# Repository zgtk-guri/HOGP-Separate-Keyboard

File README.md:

# HOGP-Separate-Keyboard
A separate keyboard with nRF51 and DAP-Link

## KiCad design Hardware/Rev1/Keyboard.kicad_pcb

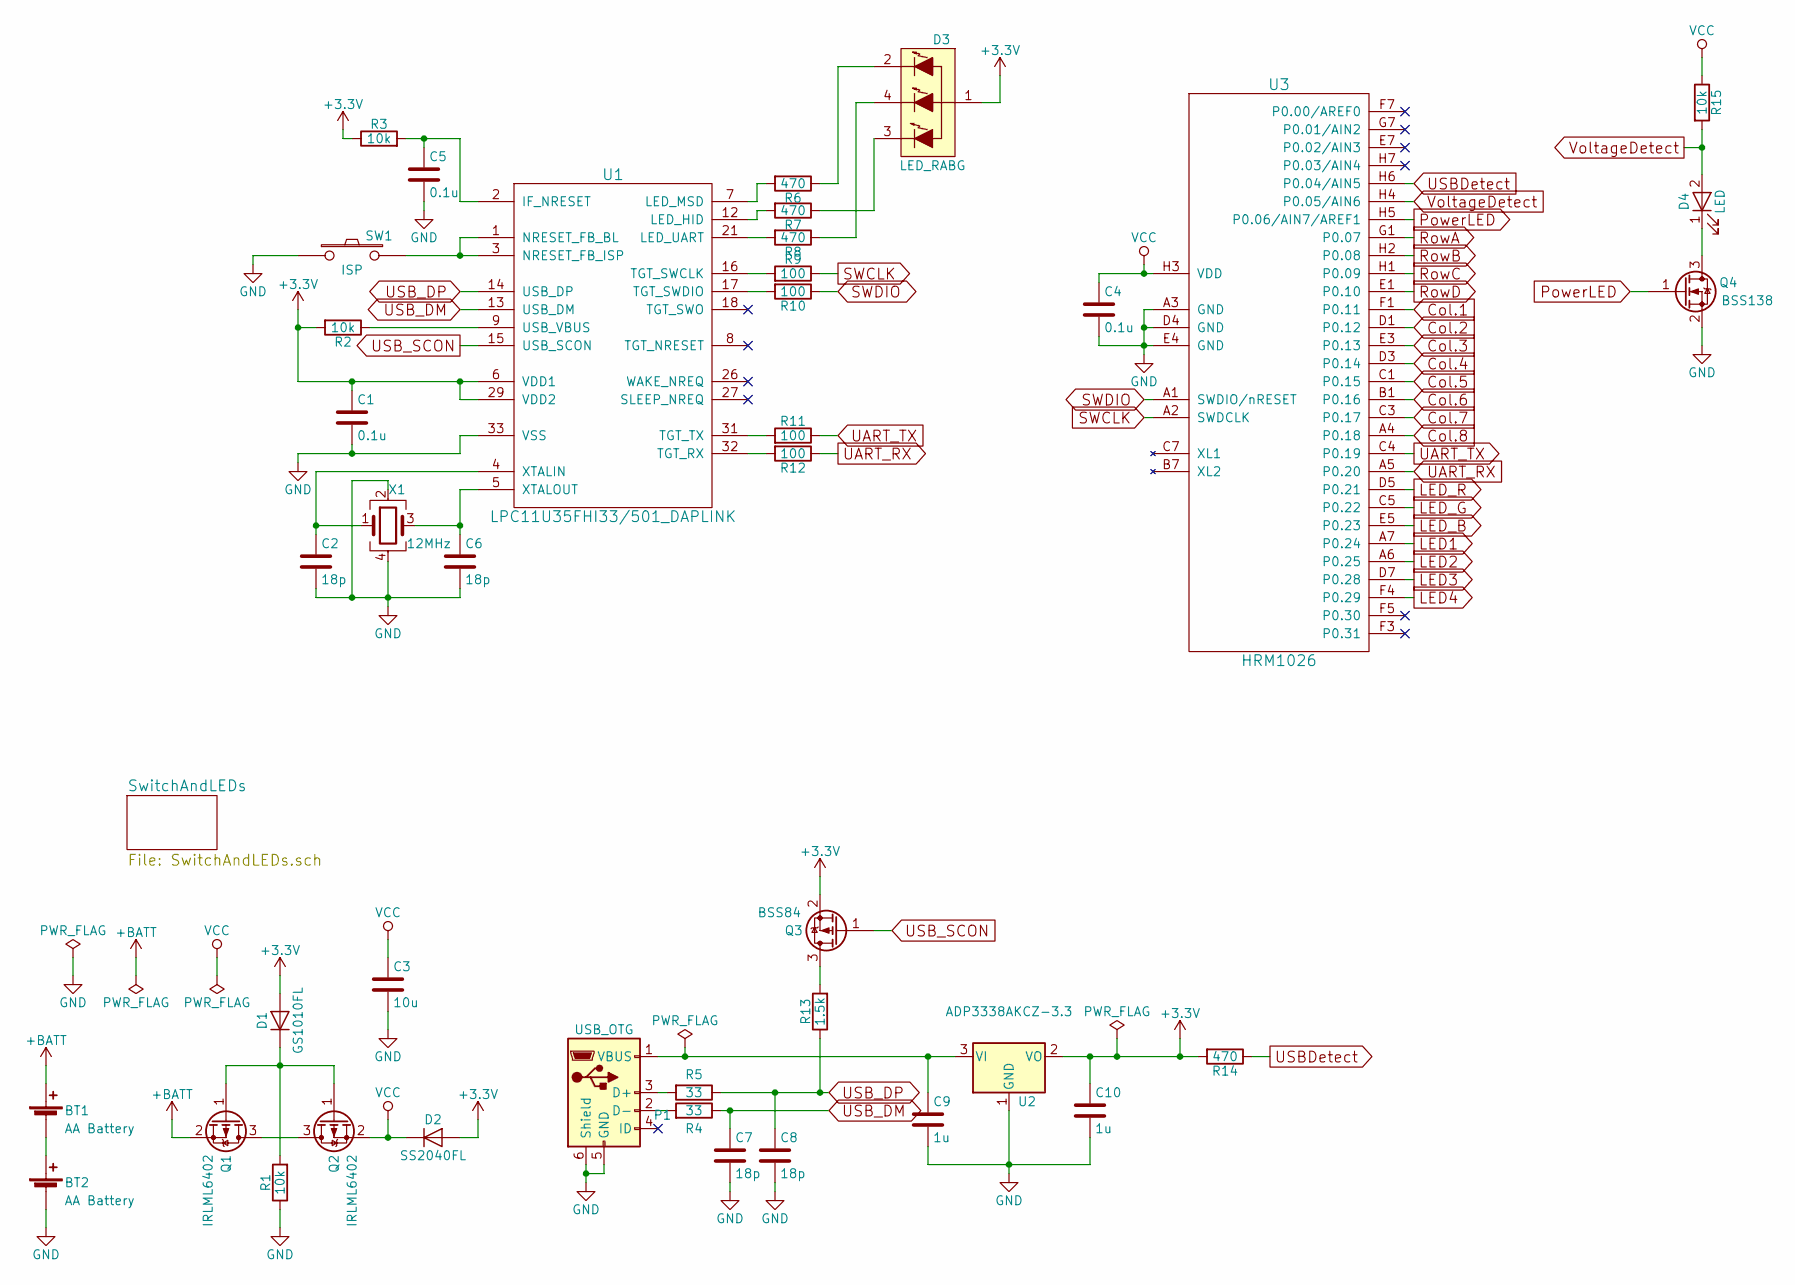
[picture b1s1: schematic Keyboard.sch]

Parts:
BT1, BT2: AA Battery; BH-311P-1
C1, C4, C5: 0.1u; C_0603
C2, C6, C7, C8: 18p; C_0603
C3: 10u; C_0805
C9, C10: 1u; C_0603
D1: GS1010FL; SOD-123
D2: SS2040FL; SOD-123
D3: LED_RABG; OSTB0603C1C-A
D4: LED; LED-0603
P1: USB_OTG; ZX62R-B-5P
Q1, Q2: IRLML6402; SOT-23
Q3: BSS84; SOT-23
Q4: BSS138; SOT-23
R1, R2, R3, R15: 10k; R_0603
R4, R5: 33; R_0603
R6, R7, R8, R14: 470; R_0603
R9, R10, R11, R12: 100; R_0603
R13: 1.5k; R_0603
SW1: ISP; SKRPACE010
U1: LPC11U35FHI33/501_DAPLINK; QFN-32-1EP_5x5mm_Pitch0.5mm
U2: ADP3338AKCZ-3.3; SOT-223
U3: HRM1026
X1: 12MHz; Crystal_SMD_3225-4pin_3.2x2.5mm

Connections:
+3V3: C1.1, C10.1, D1.2 (A), D2.2 (A), D3.1 (COMMON_ANODE), Q3.2 (S), R2.2, R3.1, R14.2, U1.6 (VDD1), U1.29 (VDD2), U2.2 (VO)
+BATT: BT1.1 (+), Q1.2 (S)
Col.1: U3.F1 (P0.11); also elsewhere on the board
Col.2: U3.D1 (P0.12); also elsewhere on the board
Col.3: U3.E3 (P0.13); also elsewhere on the board
Col.4: U3.D3 (P0.14); also elsewhere on the board
Col.5: U3.C1 (P0.15); also elsewhere on the board
Col.6: U3.B1 (P0.16); also elsewhere on the board
Col.7: U3.C3 (P0.17); also elsewhere on the board
Col.8: U3.A4 (P0.18); also elsewhere on the board
GND: BT2.2 (-), C1.2, C2.2, C3.2, C4.2, C5.2, C6.2, C7.2, C8.2, C9.2, C10.2, P1.5 (GND), P1.6 (Shield), Q4.2 (S), R1.1, SW1.1, U1.33 (VSS), U2.1 (GND), U3.A3 (GND), U3.D4 (GND), U3.E4 (GND), X1.2, X1.4; also elsewhere on the board
LED1: U3.A7 (P0.24); also elsewhere on the board
LED2: U3.A6 (P0.25); also elsewhere on the board
LED3: U3.D7 (P0.28); also elsewhere on the board
LED4: U3.F4 (P0.29); also elsewhere on the board
LED_B: U3.E5 (P0.23); also elsewhere on the board
LED_G: U3.C5 (P0.22); also elsewhere on the board
LED_R: U3.D5 (P0.21); also elsewhere on the board
unnamed: BT1.2 (-), BT2.1 (+)
unnamed: C2.1, U1.4 (XTALIN), X1.1
unnamed: C5.1, R3.2, U1.2 (IF_NRESET)
unnamed: C6.1, U1.5 (XTALOUT), X1.3
unnamed: C9.1, P1.1 (VBUS), U2.3 (VI)
unnamed: D1.1 (K), Q1.1 (G), Q2.1 (G), R1.2
unnamed: D3.2 (RED_CATHODE), R6.1
unnamed: D3.3 (BLUE_CATHODE), R7.1
unnamed: D3.4 (GREEN_CATHODE), R8.1
unnamed: D4.1 (K), Q4.3 (D)
unnamed: P1.2 (D-), R4.2
unnamed: P1.3 (D+), R5.2
unnamed: Q1.3 (D), Q2.3 (D)
unnamed: Q3.3 (D), R13.2
unnamed: R2.1, U1.9 (USB_VBUS)
unnamed: R6.2, U1.7 (LED_MSD)
unnamed: R7.2, U1.12 (LED_HID)
unnamed: R8.2, U1.21 (LED_UART)
unnamed: R9.2, U1.16 (TGT_SWCLK)
unnamed: R10.2, U1.17 (TGT_SWDIO)
unnamed: R11.2, U1.31 (TGT_TX)
unnamed: R12.2, U1.32 (TGT_RX)
unnamed: SW1.2, U1.1 (NRESET_FB_BL), U1.3 (NRESET_FB_ISP)
PowerLED: Q4.1 (G), U3.H5 (P0.06/AIN7/AREF1)
RowA: U3.G1 (P0.07); also elsewhere on the board
RowB: U3.H2 (P0.08); also elsewhere on the board
RowC: U3.H1 (P0.09); also elsewhere on the board
RowD: U3.E1 (P0.10); also elsewhere on the board
SWCLK: R9.1, U3.A2 (SWDCLK)
SWDIO: R10.1, U3.A1 (SWDIO/nRESET)
UART_RX: R12.1, U3.A5 (P0.20)
UART_TX: R11.1, U3.C4 (P0.19)
USBDetect: R14.1, U3.H6 (P0.04/AIN5)
USB_DM: C7.1, R4.1, U1.13 (USB_DM)
USB_DP: C8.1, R5.1, R13.1, U1.14 (USB_DP)
USB_SCON: Q3.1 (G), U1.15 (USB_SCON)
VCC: C3.1, C4.1, D2.1 (K), Q2.2 (S), R15.1, U3.H3 (VDD); also elsewhere on the board
VoltageDetect: D4.2 (A), R15.2, U3.H4 (P0.05/AIN6)

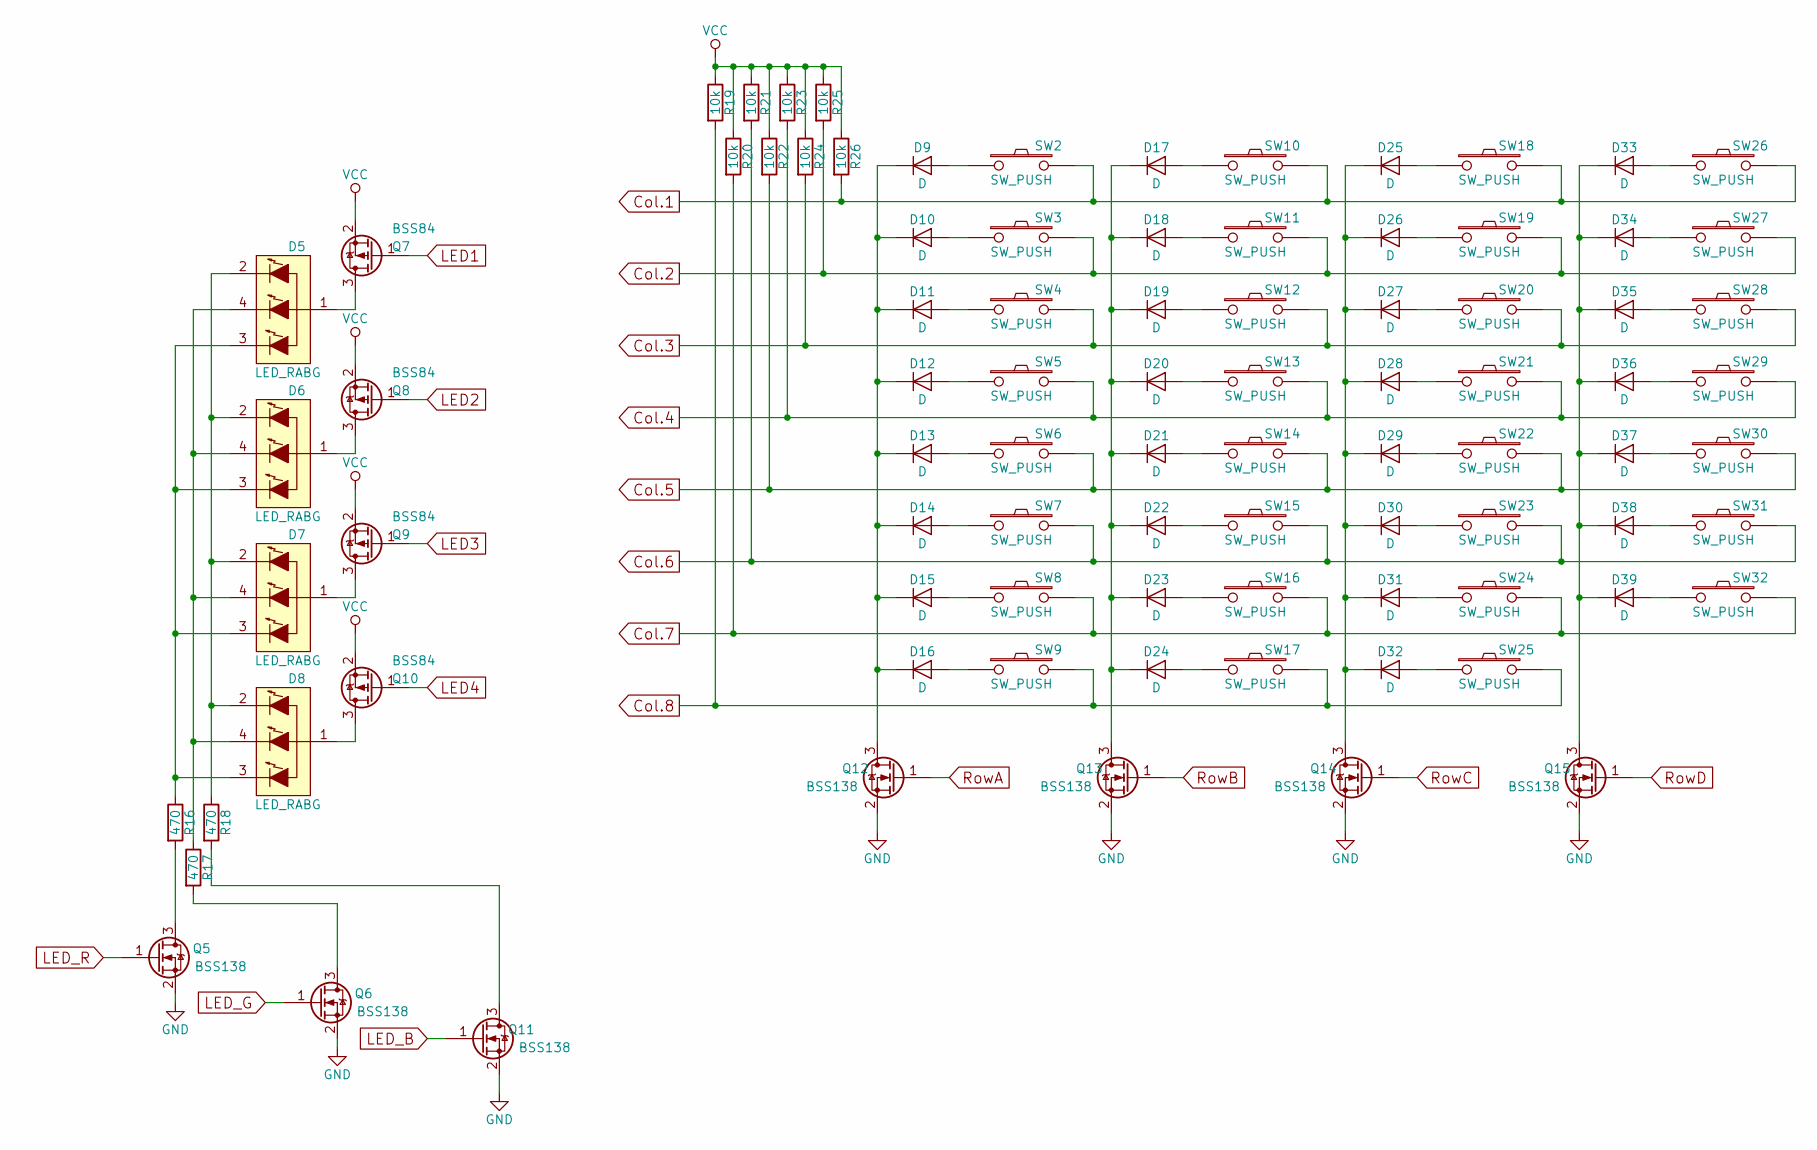
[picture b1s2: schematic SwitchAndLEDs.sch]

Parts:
D5, D6, D7, D8: LED_RABG; OSTB0603C1C-A
D9, D10, D11, D12, D13, D14, D15, D16, D17, D18, D19, D20, D21, D22, D23, D24, D25, D26, D27, D28, D29, D30, D31, D32, D33, D34, D35, D36, D37, D38, D39: D; D_SOD-123
Q5, Q6, Q11, Q12, Q13, Q14, Q15: BSS138; SOT-23
Q7, Q8, Q9, Q10: BSS84; SOT-23
R16, R17, R18: 470; R_0603
R19, R20, R21, R22, R23, R24, R25, R26: 10k; R_0603
SW2, SW3, SW4, SW5, SW6, SW7, SW8, SW9, SW10, SW11, SW12, SW13, SW14, SW15, SW16, SW17, SW18, SW19, SW20, SW21, SW22, SW23, SW24, SW25, SW26, SW27, SW28, SW29, SW30, SW31, SW32: SW_PUSH; MX_PCB_Mount

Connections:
Col.1: R26.2, SW2.2, SW10.2, SW18.2, SW26.2; also elsewhere on the board
Col.2: R25.2, SW3.2, SW11.2, SW19.2, SW27.2; also elsewhere on the board
Col.3: R24.2, SW4.2, SW12.2, SW20.2, SW28.2; also elsewhere on the board
Col.4: R23.2, SW5.2, SW13.2, SW21.2, SW29.2; also elsewhere on the board
Col.5: R22.2, SW6.2, SW14.2, SW22.2, SW30.2; also elsewhere on the board
Col.6: R21.2, SW7.2, SW15.2, SW23.2, SW31.2; also elsewhere on the board
Col.7: R20.2, SW8.2, SW16.2, SW24.2, SW32.2; also elsewhere on the board
Col.8: R19.2, SW9.2, SW17.2, SW25.2; also elsewhere on the board
GND: Q5.2 (S), Q6.2 (S), Q11.2 (S), Q12.2 (S), Q13.2 (S), Q14.2 (S), Q15.2 (S); also elsewhere on the board
LED1: Q7.1 (G); also elsewhere on the board
LED2: Q8.1 (G); also elsewhere on the board
LED3: Q9.1 (G); also elsewhere on the board
LED4: Q10.1 (G); also elsewhere on the board
LED_B: Q11.1 (G); also elsewhere on the board
LED_G: Q6.1 (G); also elsewhere on the board
LED_R: Q5.1 (G); also elsewhere on the board
unnamed: D5.1 (COMMON_ANODE), Q7.3 (D)
unnamed: D5.2 (RED_CATHODE), D6.2 (RED_CATHODE), D7.2 (RED_CATHODE), D8.2 (RED_CATHODE), R18.1
unnamed: D5.3 (BLUE_CATHODE), D6.3 (BLUE_CATHODE), D7.3 (BLUE_CATHODE), D8.3 (BLUE_CATHODE), R16.1
unnamed: D5.4 (GREEN_CATHODE), D6.4 (GREEN_CATHODE), D7.4 (GREEN_CATHODE), D8.4 (GREEN_CATHODE), R17.1
unnamed: D6.1 (COMMON_ANODE), Q8.3 (D)
unnamed: D7.1 (COMMON_ANODE), Q9.3 (D)
unnamed: D8.1 (COMMON_ANODE), Q10.3 (D)
unnamed: D9.2 (A), SW2.1
unnamed: D9.1 (K), D10.1 (K), D11.1 (K), D12.1 (K), D13.1 (K), D14.1 (K), D15.1 (K), D16.1 (K), Q12.3 (D)
unnamed: D10.2 (A), SW3.1
unnamed: D11.2 (A), SW4.1
unnamed: D12.2 (A), SW5.1
unnamed: D13.2 (A), SW6.1
unnamed: D14.2 (A), SW7.1
unnamed: D15.2 (A), SW8.1
unnamed: D16.2 (A), SW9.1
unnamed: D17.1 (K), D18.1 (K), D19.1 (K), D20.1 (K), D21.1 (K), D22.1 (K), D23.1 (K), D24.1 (K), Q13.3 (D)
unnamed: D17.2 (A), SW10.1
unnamed: D18.2 (A), SW11.1
unnamed: D19.2 (A), SW12.1
unnamed: D20.2 (A), SW13.1
unnamed: D21.2 (A), SW14.1
unnamed: D22.2 (A), SW15.1
unnamed: D23.2 (A), SW16.1
unnamed: D24.2 (A), SW17.1
unnamed: D25.1 (K), D26.1 (K), D27.1 (K), D28.1 (K), D29.1 (K), D30.1 (K), D31.1 (K), D32.1 (K), Q14.3 (D)
unnamed: D25.2 (A), SW18.1
unnamed: D26.2 (A), SW19.1
unnamed: D27.2 (A), SW20.1
unnamed: D28.2 (A), SW21.1
unnamed: D29.2 (A), SW22.1
unnamed: D30.2 (A), SW23.1
unnamed: D31.2 (A), SW24.1
unnamed: D32.2 (A), SW25.1
unnamed: D33.1 (K), D34.1 (K), D35.1 (K), D36.1 (K), D37.1 (K), D38.1 (K), D39.1 (K), Q15.3 (D)
unnamed: D33.2 (A), SW26.1
unnamed: D34.2 (A), SW27.1
unnamed: D35.2 (A), SW28.1
unnamed: D36.2 (A), SW29.1
unnamed: D37.2 (A), SW30.1
unnamed: D38.2 (A), SW31.1
unnamed: D39.2 (A), SW32.1
unnamed: Q5.3 (D), R16.2
unnamed: Q6.3 (D), R17.2
unnamed: Q11.3 (D), R18.2
RowA: Q12.1 (G); also elsewhere on the board
RowB: Q13.1 (G); also elsewhere on the board
RowC: Q14.1 (G); also elsewhere on the board
RowD: Q15.1 (G); also elsewhere on the board
VCC: Q7.2 (S), Q8.2 (S), Q9.2 (S), Q10.2 (S), R19.1, R20.1, R21.1, R22.1, R23.1, R24.1, R25.1, R26.1; also elsewhere on the board

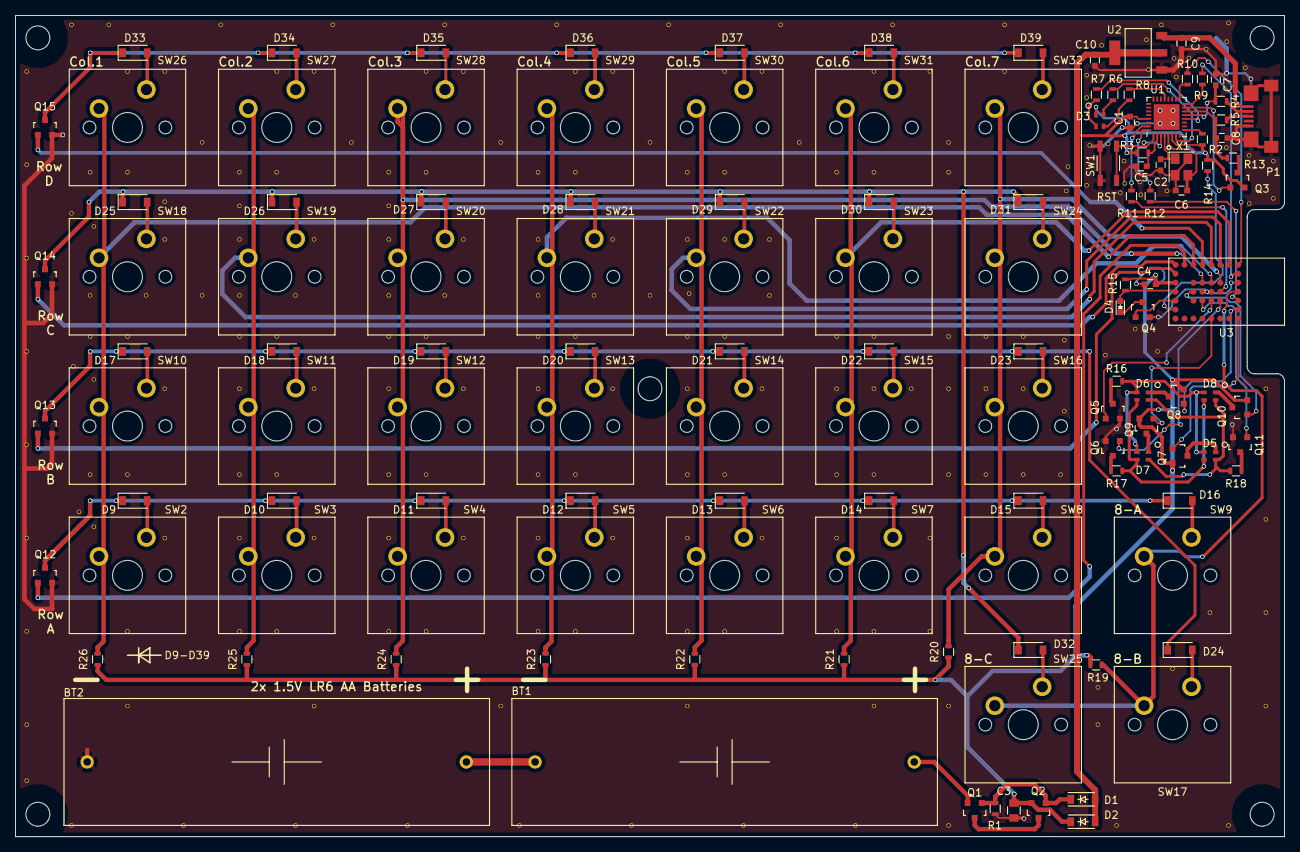
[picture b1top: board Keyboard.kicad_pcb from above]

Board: 2 copper layers, 170.0 x 110.0 mm, 129 parts (0 on the bottom side), 101 nets.

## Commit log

2018-01-02 Add Rev1 Schematic
2018-01-02 Annotate Schematic
2018-01-03 Change RGB-LED Symbols and assign PCB Footprints
2018-01-03 Import netlist to Pcbnew
2018-01-06 Fix schematic
2018-01-20 Add Rev1 Left PCB Pattern
2018-01-30 output gerbver
